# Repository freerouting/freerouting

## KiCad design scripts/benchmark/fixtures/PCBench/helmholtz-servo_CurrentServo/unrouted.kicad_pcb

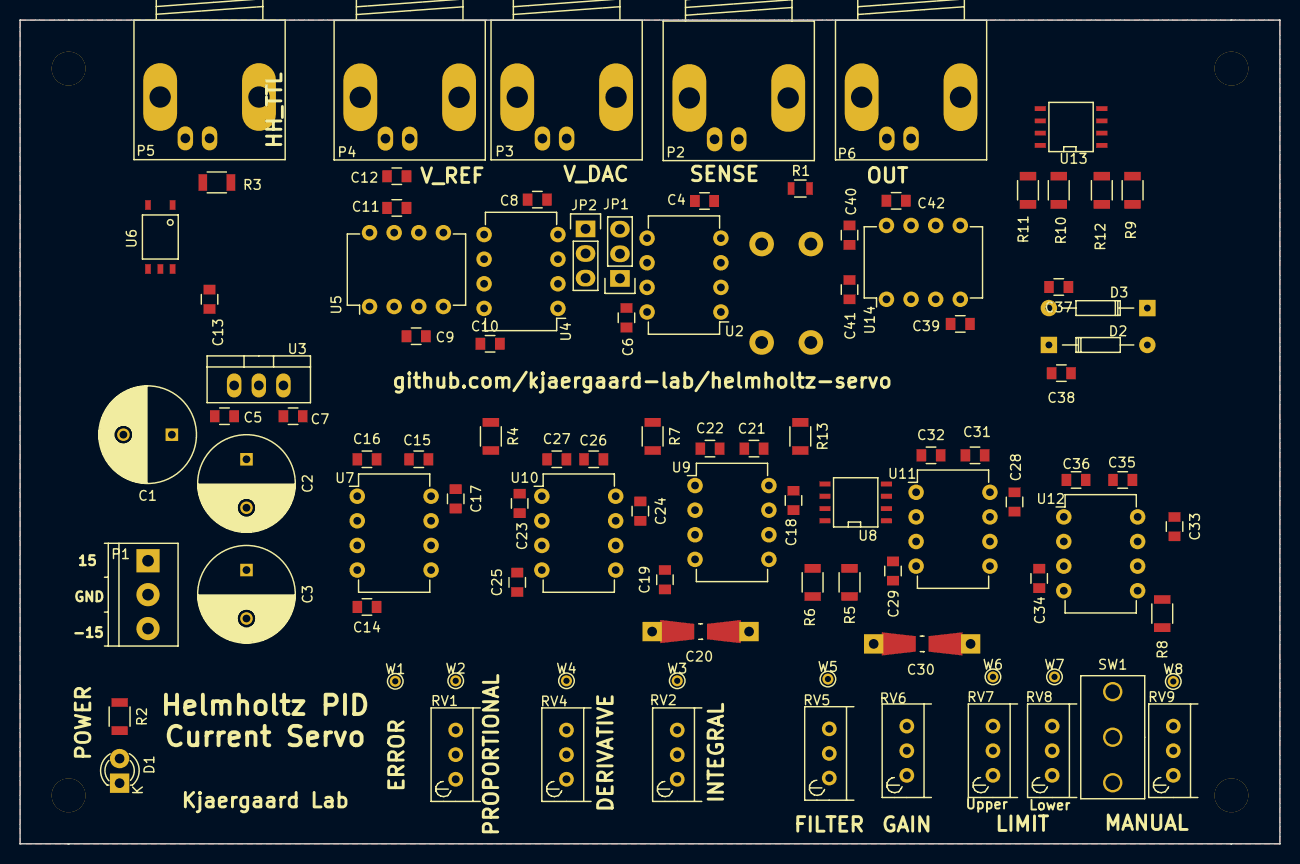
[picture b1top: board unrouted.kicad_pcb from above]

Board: 2 copper layers, 130.0 x 85.0 mm, 97 parts (1 on the bottom side), 52 nets, no tracks yet.

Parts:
C1: 22u; C_Radial_D10_L13_P5
C2, C3: 100u; C_Radial_D10_L16_P5
C4, C6, C8, C10, C12, C13, C14, C15, C16, C17, C18, C19, C21, C22, C23, C24, C25, C26, C27, C28, C29, C31, C32, C33, C34, C35, C36, C37, C38, C39, C40, C41, C42: 100n; C_0805
C5: 330n; C_0805
C7: 10n; C_0805
C9, C11: 2.2u; C_0805
C20, C30: 100n; Resistor_SMD+THTuniversal_0805to1206_RM10_HandSoldering
D1: LED; LED-3MM
D2, D3: D; Diode_DO-35_SOD27_Horizontal_RM10
JP1, JP2: JUMPER3; Pin_Header_Straight_1x03
P1: POWER; TerminalBlock_Pheonix_PT-3.5mm_3pol
P2: SENSE; BNC_Socket_TYCO-AMP_LargePads
P3: V_DAC; BNC_Socket_TYCO-AMP_LargePads
P4: VREF; BNC_Socket_TYCO-AMP_LargePads
P5: HH_IN; BNC_Socket_TYCO-AMP_LargePads
P6: OUT; BNC_Socket_TYCO-AMP_LargePads
R1: 0R; R_0805
R2: 1K2; R_1206
R3: 330; R_1206
R4, R7, R13: 10K; R_1206
R5, R10, R12: DNP; R_1206
R6: 3K3; R_1206
R8: 51K; R_1206
R9, R11: 50; R_1206
RV1, RV2, RV4, RV5, RV9: 10K; Potentiometer_Bourns_3296W_3-8Zoll_Inline_ScrewUp
RV6: 100K; Potentiometer_Bourns_3296W_3-8Zoll_Inline_ScrewUp
RV7, RV8: 2K; Potentiometer_Bourns_3296W_3-8Zoll_Inline_ScrewUp
SW1: 1AS2T2B4M2RE; Switch_SPDT_4.7mm
U1: VHP4Z
U2, U4: INA105; DIP-8_W7.62mm
U3: 78L05; TO-220_Neutral123_Vertical
U5: MAX6350; DIP-8_W7.62mm
U6: TLP116A
U7, U9, U10, U11, U12, U14: TC7650; DIP-8_W7.62mm
U8, U13: DG419; SOIC-8-N
W1: ERROR; PINTST
W2: PROP; PINTST
W3: INT; PINTST
W4: DERIV; PINTST
W5: FILTER; PINTST
W6: ULIM; PINTST
W7: LLIM; PINTST
W8: MANUAL; PINTST

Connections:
/OutputConditioning/CTRL_IN: C30.2, R4.1, R7.1, R13.1, RV5.1, U11.2
/OutputConditioning/LLIMIT: C37.2, D3.2, RV8.2, W7.1
/OutputConditioning/SIG_OUT: P6.1, U14.2, U14.6
/OutputConditioning/ULIMIT: C38.2, D2.1, RV7.2, W6.1
/PIDAmps/ERROR: C23.2, RV1.1, RV2.1, U4.5, U4.6, W1.1
GND: C2.2, C3.1, C4.2, C5.2, C6.1, C7.2, C8.1, C9.2, C10.1, C11.2, C12.2, C13.2, C14.1, C17.1, C18.1, C19.1, C24.1, C25.1, C28.1, C29.1, C33.1, C34.1, C37.1, C38.1, C39.2, C42.1, P1.2, P3.2, P4.2, P6.2, R1.2, R11.2, R12.2, U2.1, U3.2, U4.1, U5.4, U6.4, U7.3, U8.3, U9.3, U10.3, U11.3, U12.3, U13.3
HH_TTL: U6.5, U8.6, U13.6
unnamed: C11.1, C12.1, P4.1, U5.6
unnamed: C15.1, U7.8
unnamed: C16.1, U7.1
unnamed: C20.1, R5.1, R6.1, R13.2, U9.6, W3.1
unnamed: C20.2, RV2.2, RV2.3, U8.1, U9.2
unnamed: C21.1, U9.8
unnamed: C22.1, U9.1
unnamed: C23.1, RV4.1, U10.2
unnamed: C26.1, U10.8
unnamed: C27.1, U10.1
unnamed: C30.1, RV5.2, RV5.3, RV6.3, U11.6, W5.1
unnamed: C31.1, U11.8
unnamed: C32.1, U11.1
unnamed: C35.1, U12.8
unnamed: C36.1, U12.1
unnamed: C40.1, U14.8
unnamed: C41.1, U14.1
unnamed: D1.2, R2.2
unnamed: D2.2, D3.1, R8.1, SW1.1
unnamed: JP1.1, JP2.3, U4.2
unnamed: JP1.2, P3.1
unnamed: JP1.3, JP2.1, U4.3
unnamed: JP2.2, U2.5, U2.6
unnamed: P2.1, U1.1
unnamed: P2.2, R1.1, U1.2
unnamed: P5.1, R3.2
unnamed: P5.2, U6.3
unnamed: R3.1, U6.1
unnamed: R4.2, RV1.3, U7.6, W2.1
unnamed: R5.2, U8.2
unnamed: R6.2, U8.8
unnamed: R7.2, RV4.2, RV4.3, U10.6, W4.1
unnamed: R8.2, RV6.1, U12.6
unnamed: R10.1, R11.1, U13.8
unnamed: R9.2, R10.2, SW1.2
unnamed: R9.1, R12.1, U13.2
unnamed: RV1.2, U7.2
unnamed: RV6.2, U12.2
unnamed: RV9.2, SW1.3, W8.1
unnamed: U1.3, U2.3
unnamed: U1.4, U2.2
unnamed: U13.1, U14.3
VCC: C7.1, C13.1, U3.3, U6.6, U8.5, U13.5
VDD: C1.1, C2.1, C5.1, C6.2, C9.1, C10.2, C17.2, C18.2, C24.2, C28.2, C33.2, C42.2, P1.1, R2.1, RV7.1, RV8.1, RV9.1, U2.7, U3.1, U4.7, U5.2, U7.7, U8.4, U9.7, U10.7, U11.7, U12.7, U13.4, U14.7
VSS: C1.2, C3.2, C4.1, C8.2, C14.2, C15.2, C16.2, C19.2, C21.2, C22.2, C25.2, C26.2, C27.2, C29.2, C31.2, C32.2, C34.2, C35.2, C36.2, C39.1, C40.2, C41.2, D1.1, P1.3, RV7.3, RV8.3, RV9.3, U2.4, U4.4, U7.4, U8.7, U9.4, U10.4, U11.4, U12.4, U13.7, U14.4

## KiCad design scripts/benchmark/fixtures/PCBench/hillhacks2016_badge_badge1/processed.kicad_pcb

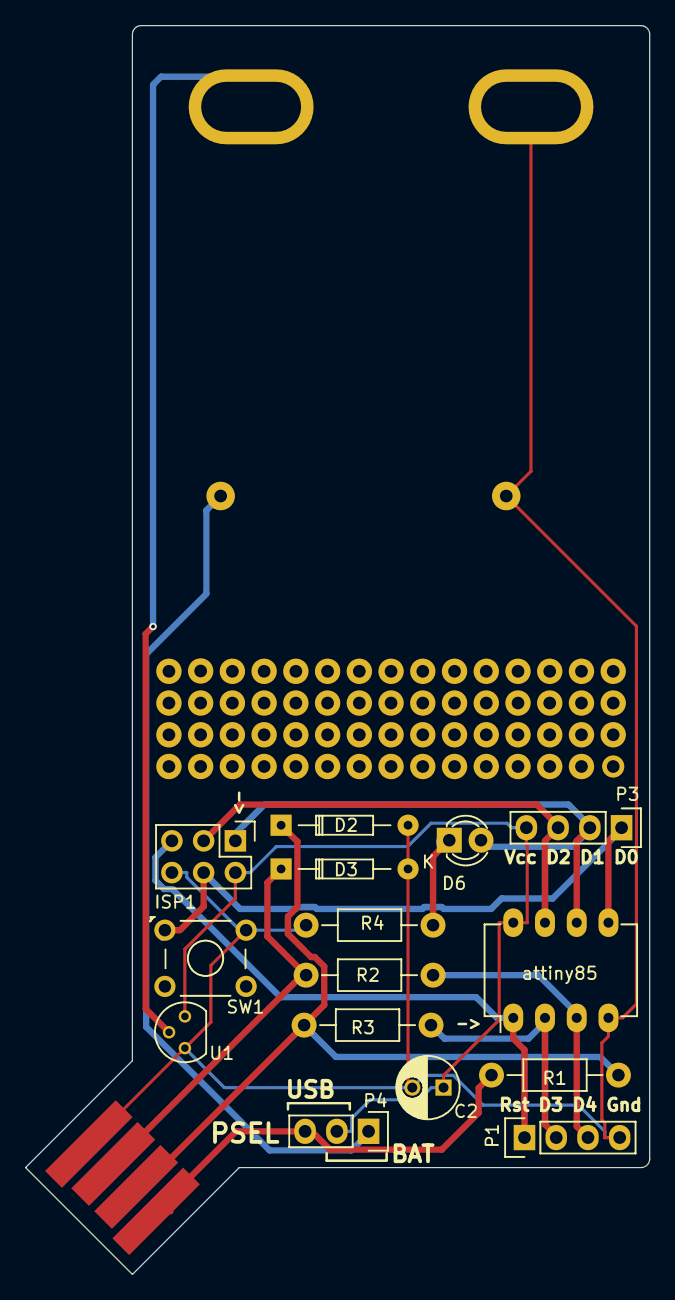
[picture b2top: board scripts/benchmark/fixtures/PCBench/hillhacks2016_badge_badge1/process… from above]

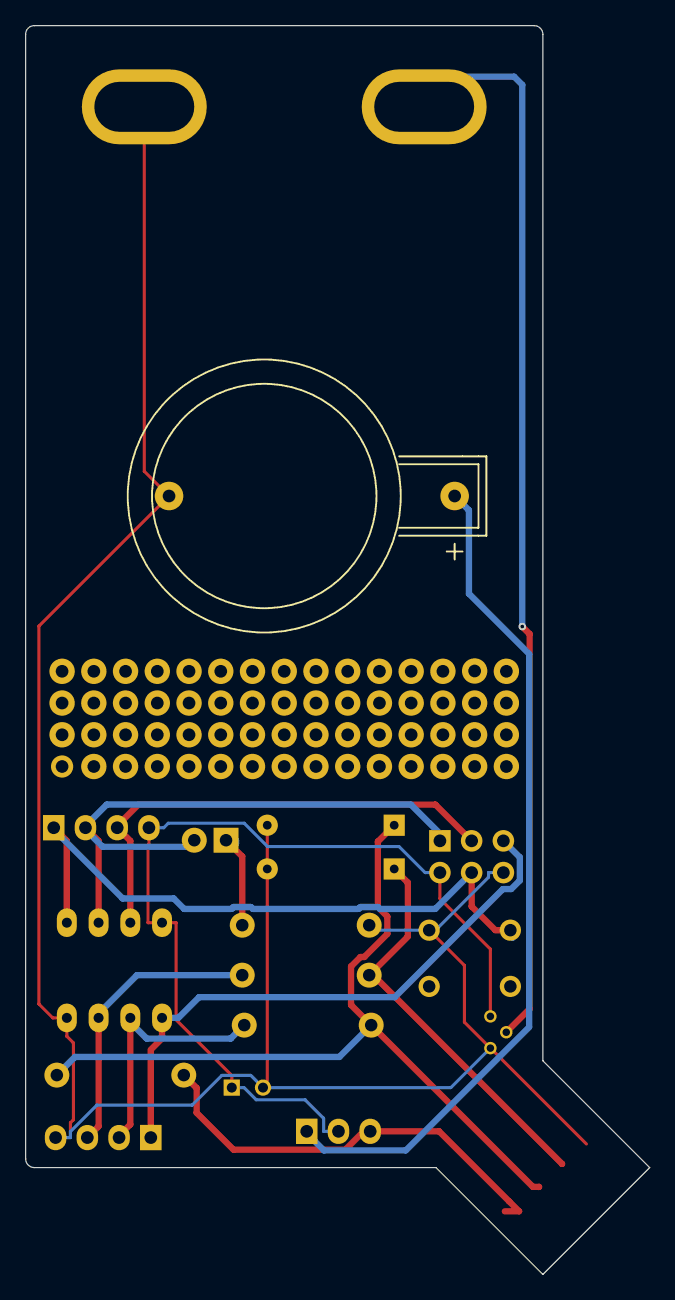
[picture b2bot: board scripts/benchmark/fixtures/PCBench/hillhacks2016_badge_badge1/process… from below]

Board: 2 copper layers, 50.0 x 100.0 mm, 22 parts (2 on the bottom side), 14 nets.

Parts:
BT1: Battery; CR2032H
C2: 4.7uF; C_Radial_D5_L11_P2.5
D2, D3: 3.6V BZX79C3V6; Diode_DO-35_SOD27_Horizontal_RM10
D6: LED; LED-3MM
ISP1: AVR-ISP-6; Pin_Header_Straight_2x03
P1, P3: CONN_01X04; Pin_Header_Straight_1x04
P2: USB_A; usb-PCB
P4: CONN_01X03; Pin_Header_Straight_1x03
R1: 1.5k; Resistor_Horizontal_RM10mm
R2, R3: 68; Resistor_Horizontal_RM10mm
R4: 470; Resistor_Horizontal_RM10mm
SW1: SW_PUSH; OPL_DIP_BUTTON_TS-1109_BEST_SHENZEN
U1: MCP1700-3302E/TO; TO-92_Molded_Narrow
U4: proto_area
U5, U6: badge_hole2; badge_hole_6mmx3mm(+2mmCu)
U7, U8: custom_logo; tesseract
attiny85: ATTINY85-S; DIP-8_W7.62mm_LongPads

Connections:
/D0: ISP1.4, P3.1, SW1.1, attiny85.5
/D1: D6.2, ISP1.1, P3.2, attiny85.6
/D2: ISP1.3, P3.3, attiny85.7
/D3: P1.2, R3.2, attiny85.2
/D4: P1.3, R2.2, attiny85.3
/RST: ISP1.5, P1.1, attiny85.1
/USB-D+: D3.1, P2.3, R2.1
/USB-D-: D2.1, P2.2, R1.1, R3.1
/VBAT: BT1.1, P4.1
/VBUS: P2.1, P4.3, R1.2
/V_sec_bat: U1.2, U5.1
GND: BT1.2, C2.2, D2.2, D3.2, ISP1.6, P1.4, P2.4, R4.2, SW1.2, U1.1, U6.1, attiny85.4
unnamed: D6.1, R4.1
VCC: C2.1, ISP1.2, P3.4, P4.2, U1.3, attiny85.8

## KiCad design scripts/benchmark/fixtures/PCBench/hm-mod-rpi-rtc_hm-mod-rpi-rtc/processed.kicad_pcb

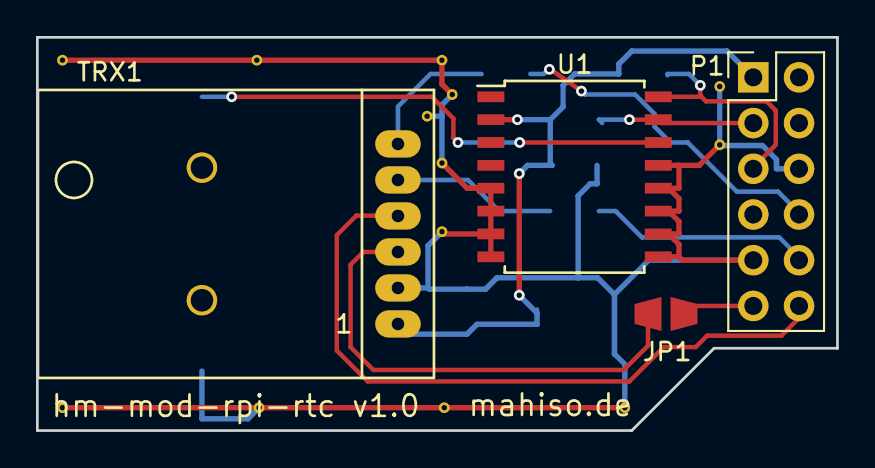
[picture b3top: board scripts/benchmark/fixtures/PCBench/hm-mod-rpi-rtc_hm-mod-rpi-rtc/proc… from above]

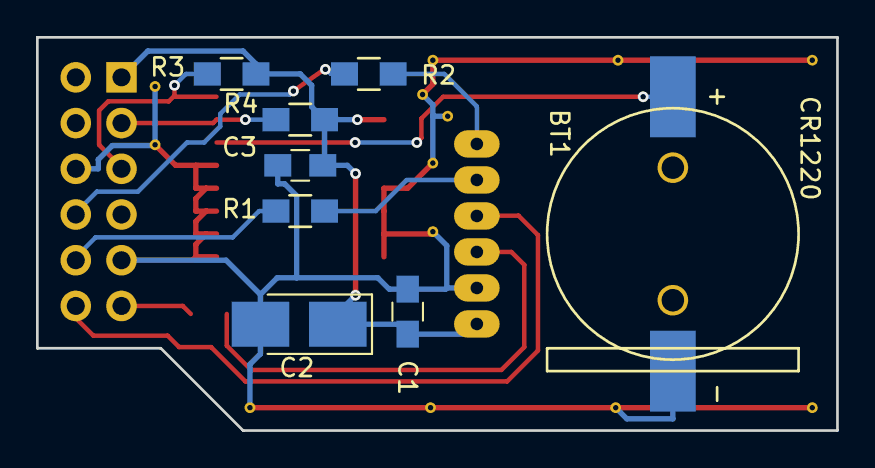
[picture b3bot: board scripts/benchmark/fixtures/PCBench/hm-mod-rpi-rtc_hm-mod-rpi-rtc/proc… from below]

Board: 2 copper layers, 44.5 x 21.8 mm, 12 parts (8 on the bottom side), 12 nets.

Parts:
BT1: CR1220; CR1220_holder
C1, C3: 100n; C_0805_HandSoldering
C2: 100u/10V; CP_Tantalum_Case-B_EIA-3528-21_Hand
JP1: Prog; solder_jumper
P1: RPI CONN; Pin_Header_Straight_2x06_Pitch2.54mm
R1, R2: 1k; R_0805_HandSoldering
R3, R4: 4.7K; R_0805_HandSoldering
TRX1: HM-MOD-UART
U1: DS3231; SOIC-16W_7.5x10.3mm_Pitch1.27mm

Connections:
/PROG: JP1.1, P1.11
/RESET: P1.12, TRX1.4
/RX: P1.8, R2.1
/SCL: P1.5, R3.2, U1.16
/SDA: P1.3, R4.2, U1.15
/TX: P1.10, R1.1
GND: BT1.2, C1.2, C2.2, C3.2, P1.6, P1.9, TRX1.2, U1.5, U1.6, U1.7, U1.8, U1.9, U1.10, U1.11, U1.12, U1.13
unnamed: BT1.1, U1.14
unnamed: JP1.2, TRX1.3
unnamed: R1.2, TRX1.5
unnamed: R2.2, TRX1.6
VCC: C1.1, C2.1, C3.1, P1.1, R3.1, R4.1, TRX1.1, U1.2

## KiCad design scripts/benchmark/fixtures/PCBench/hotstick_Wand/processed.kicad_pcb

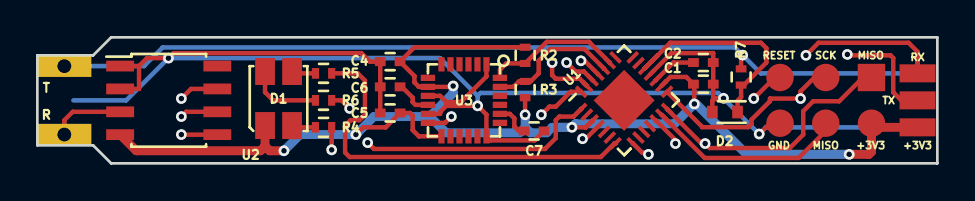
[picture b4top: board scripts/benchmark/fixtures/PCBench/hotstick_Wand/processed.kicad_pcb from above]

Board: 4 copper layers, 50.0 x 7.0 mm, 20 parts (1 on the bottom side), 24 nets.

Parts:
C1, C2, C4, C6: 100n; C_0402
C5: 10n; C_0402
C7: 2.2n; C_0402
D1: ASMB-MTB0-0A3A2; Tri-Colour_LED
D2: 3V3; SOD-523
P1: ISP; ISP_pads_2x3
P2: KLB4; Jack_3.5mm_KLB
P3: BASE; Base_Connector
R2, R3: 10k; R_0402
R4: 68R; R_0402
R5, R6: 10R; R_0402
R7: 10K; R_0402
U1: ATMEGA328-MMH; QFN-28-1EP_4x4mm_Pitch0.45mm
U2: MAX31855KASA+; SOIC-8_3.9x4.9mm_Pitch1.27mm
U3: MPU-6050

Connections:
+3V3: C1.1, C4.2, C5.2, D1.1, P1.2, P3.1, R2.1, R3.1, U1.3, U1.16, U2.4, U3.8, U3.13
/HEAT: P2.T, P3.2, R7.1
/HEAT_DETECT: D2.1, R7.2, U1.19
/LED_B: R6.1, U1.8
/LED_G: R5.1, U1.7
/LED_R: R4.1, U1.1
/MISO: P1.1, U1.14, U2.7
/MOSI: P1.4, U1.13
/MPU_INT: U1.28, U3.12
/RESET: P1.5, U1.25
/RX: P3.3, U1.26
/SCK: P1.3, U1.15, U2.5
/SCL: R3.2, U1.24, U3.23
/SDA: R2.2, U1.23, U3.24
/SENS: P2.R, U2.3
/TIP_TEMP_SELECT: U1.12, U2.6
/TX: P3.4, U1.27
GND: C1.2, C2.2, C4.1, C5.1, C6.1, C7.1, D2.2, P1.6, P2.S, P3.5, U1.4, U1.18, U2.1, U2.2, U3.1, U3.9, U3.11, U3.18
unnamed: C2.1, U1.17
unnamed: C6.2, U3.10
unnamed: C7.2, U3.20
unnamed: D1.2, R6.2
unnamed: D1.3, R5.2
unnamed: D1.4, R4.2
